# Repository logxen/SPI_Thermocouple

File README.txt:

This is a simple 1 layer breakout board for the MAX31855 digital thermocouple reader.

Bill of Materials:

1x - 1" x 0.75" single sided copper clad board (pcb)
1x - MAX31855 digital thermocouple ic, 8 pin soic (main ic)
1x - 0.1uF cap, 1206 (power filter)
1x - 10nF cap, 0603 (thermocouple filter)
1x - 1x8 0.1" pin header + 1x4 0.1" pin header
1x - 1x2 0.1" pin header or 2pos 3.5mm screw terminal (thermocouple port: t+, t-)

NOTES:

- the .png file has descriptive layers, the .bmp files are the b/w images for etching, solder mask, silk screen, and solder paste.

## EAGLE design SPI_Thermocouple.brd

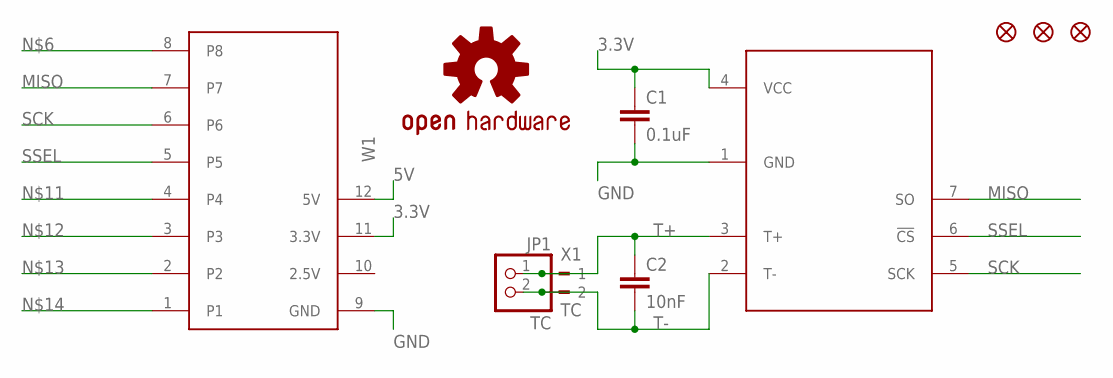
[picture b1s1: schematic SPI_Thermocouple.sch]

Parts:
C1: 0.1uF; 1206
C2: 10nF; 0603-CAP
FID1, FID2, FID3: FIDUCIAL1X2; FIDUCIAL-1X2
JP1: TC; 1X02
U1: MAX31855; SO08
U$1: OSHW-LOGOS; OSHW-LOGO-S
W1: PAPILIO-WING-8BITS
X1: TC; 180-2

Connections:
3.3V: C1.1, U1.4 (VCC), W1.11 (3.3V)
5V: W1.12 (5V)
GND: C1.2, U1.1 (GND), W1.9 (GND)
MISO: U1.7 (SO), W1.7
SCK: U1.5 (SCK), W1.6
SSEL: U1.6 (!CS), W1.5
T+: C2.1, JP1.1, U1.3 (T+), X1.1
T-: C2.2, JP1.2, U1.2 (T-), X1.2

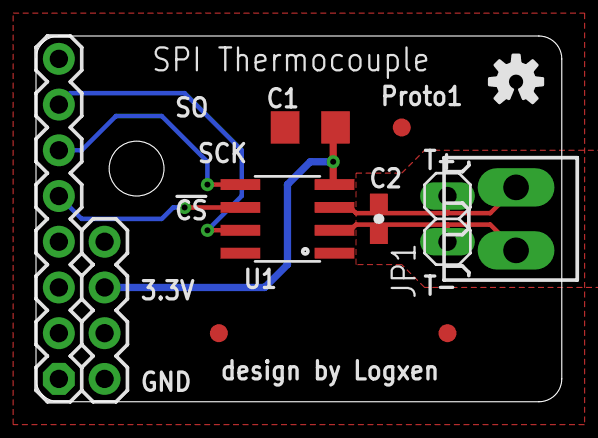
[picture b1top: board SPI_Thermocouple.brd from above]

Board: 2 copper layers, 29.2 x 20.3 mm, 10 parts (0 on the bottom side), 7 nets.

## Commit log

2012-07-11 straightened the traces from the thermocouple
2014-04-05 upgrade design to a wing
2014-10-20 removed word "tantalum" from recommended bom

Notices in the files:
parts and their libraries:
SparkFun: Licensing: CC v3.0 Share-Alike You are welcome to use this library for commercial purposes.
